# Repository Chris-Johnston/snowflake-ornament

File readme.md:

# Snowflake-Ornament

A snowflake shaped Xmas ornament with blinking LEDs.

This uses an ATTiny85 to drive 6 blue LEDs which are multiplexed.
There's a button on the front which is used to toggle display modes
and sleep.

When sleeping, the ornament uses about 200 microamps of current, little enough to run
off of a coin cell battery for about 1000 hours (in reality, probably less. I don't know, I didn't measure it)! While running, it uses about 2 milliamps,
which could last for about 120 hours.

The part was designed using KiCad. The shape of the PCB was generated with
[svg2mod]. The [outline of the board was modified from Wikipedia (Public Domain)](https://en.wikipedia.org/wiki/File:Snow_flake.svg), I added a hexagon in the
center to make room for the button, ATTiny85, and battery.

[svg2mod]: https://github.com/svg2mod/svg2mod

## Requirements

I use [damellis/attiny] for ATTiny85 support in the Arduino editor (via the VSCode extension).

[damellis/attiny]: https://github.com/damellis/attiny

## Bill of Materials

| Reference | Item |
| --------- | ---- |
| U1 | Attiny85V |
| R1, R2, R3, R4 | 50 ohm 1206 resistor |
| R5 | 10k 1206 resistor |
| C1 | 1 uf 1206 capacitor |
| D1 - D6 | 0603 LED |
| SW1 | 6x6mm SMD Pushbutton |
| BT1 | CR2023 Battery Holder |

Yes, the traces aren't parallel to the edges of the board, and yes it bugs me too.

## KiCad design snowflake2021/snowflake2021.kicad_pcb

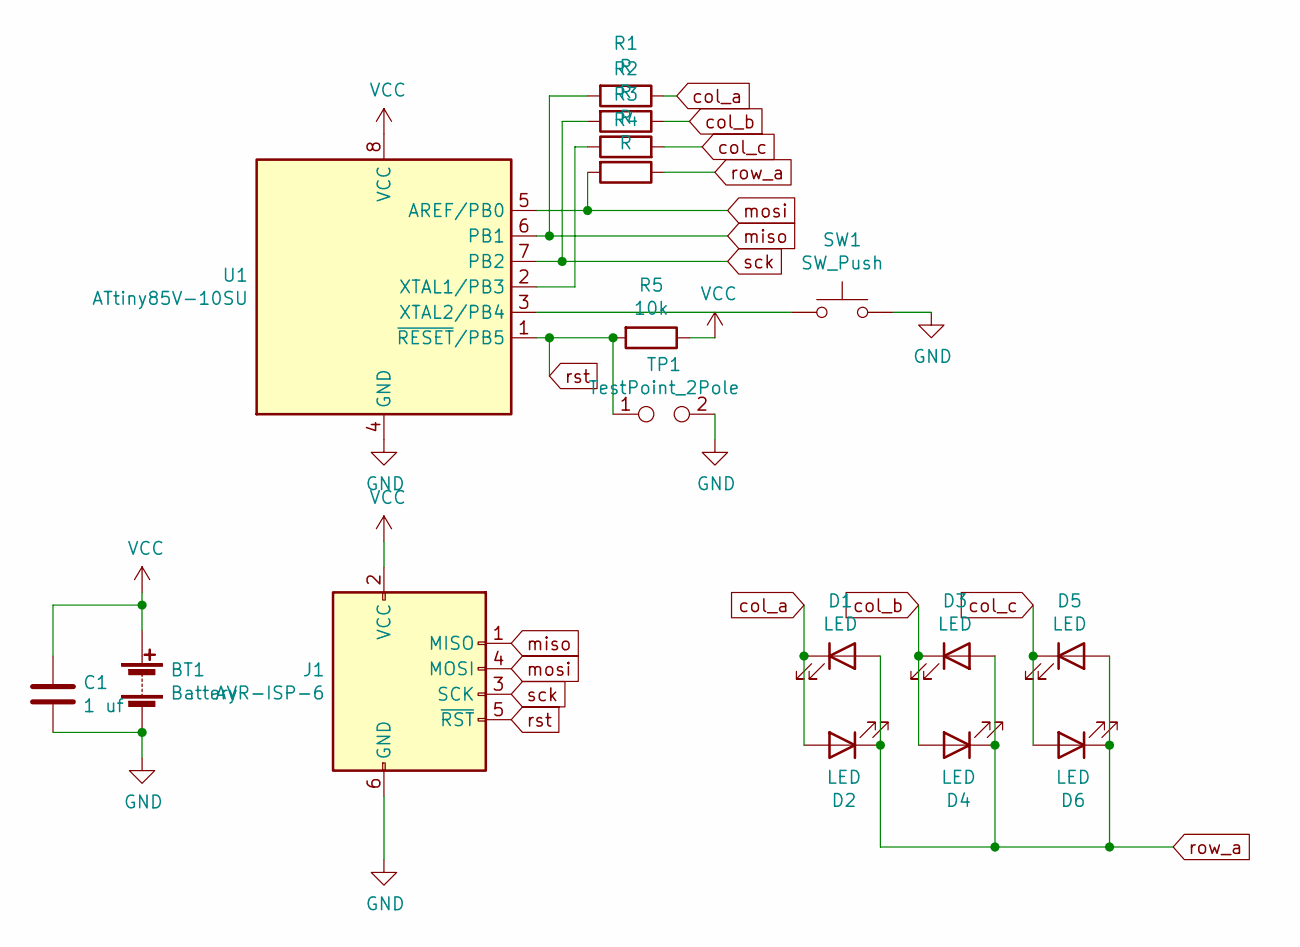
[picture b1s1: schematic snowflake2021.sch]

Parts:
BT1: Battery; BatteryHolder_ComfortableElectronic_CH273-2450_1x2450
C1: 1 uf; C_1206_3216Metric_Pad1.42x1.75mm_HandSolder
D1, D2, D3, D4, D5, D6: LED; LED_0603_1608Metric_Pad1.05x0.95mm_HandSolder
J1: AVR-ISP-6; PinHeader_2x03_P2.54mm_Vertical
R1, R2, R3, R4: R; R_1206_3216Metric_Pad1.42x1.75mm_HandSolder
R5: 10k; R_1206_3216Metric_Pad1.42x1.75mm_HandSolder
SW1: SW_Push; SW_Push_1P1T_NO_6x6mm_H9.5mm
TP1: TestPoint_2Pole; SolderJumper-2_P1.3mm_Open_Pad1.0x1.5mm
U1: ATtiny85V-10SU; SOIJ-8_5.3x5.3mm_P1.27mm

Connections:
GND: BT1.2 (-), C1.2, J1.6 (GND), SW1.2, TP1.2, U1.4 (GND); also elsewhere on the board
unnamed: R3.1, U1.2 (XTAL1/PB3)
unnamed: SW1.1, U1.3 (XTAL2/PB4)
VCC: BT1.1 (+), C1.1, J1.2 (VCC), R5.1, U1.8 (VCC)
col_a: D1.1 (K), D2.2 (A), R1.1
col_b: D3.1 (K), D4.2 (A), R2.1
col_c: D5.1 (K), D6.2 (A), R3.2
miso: J1.1 (MISO), R1.2, U1.6 (PB1)
mosi: J1.4 (MOSI), R4.2, U1.5 (AREF/PB0)
row_a: D1.2 (A), D2.1 (K), D3.2 (A), D4.1 (K), D5.2 (A), D6.1 (K), R4.1
rst: J1.5 (~RST), R5.2, TP1.1, U1.1 (~RESET~/PB5); also elsewhere on the board
sck: J1.3 (SCK), R2.2, U1.7 (PB2)

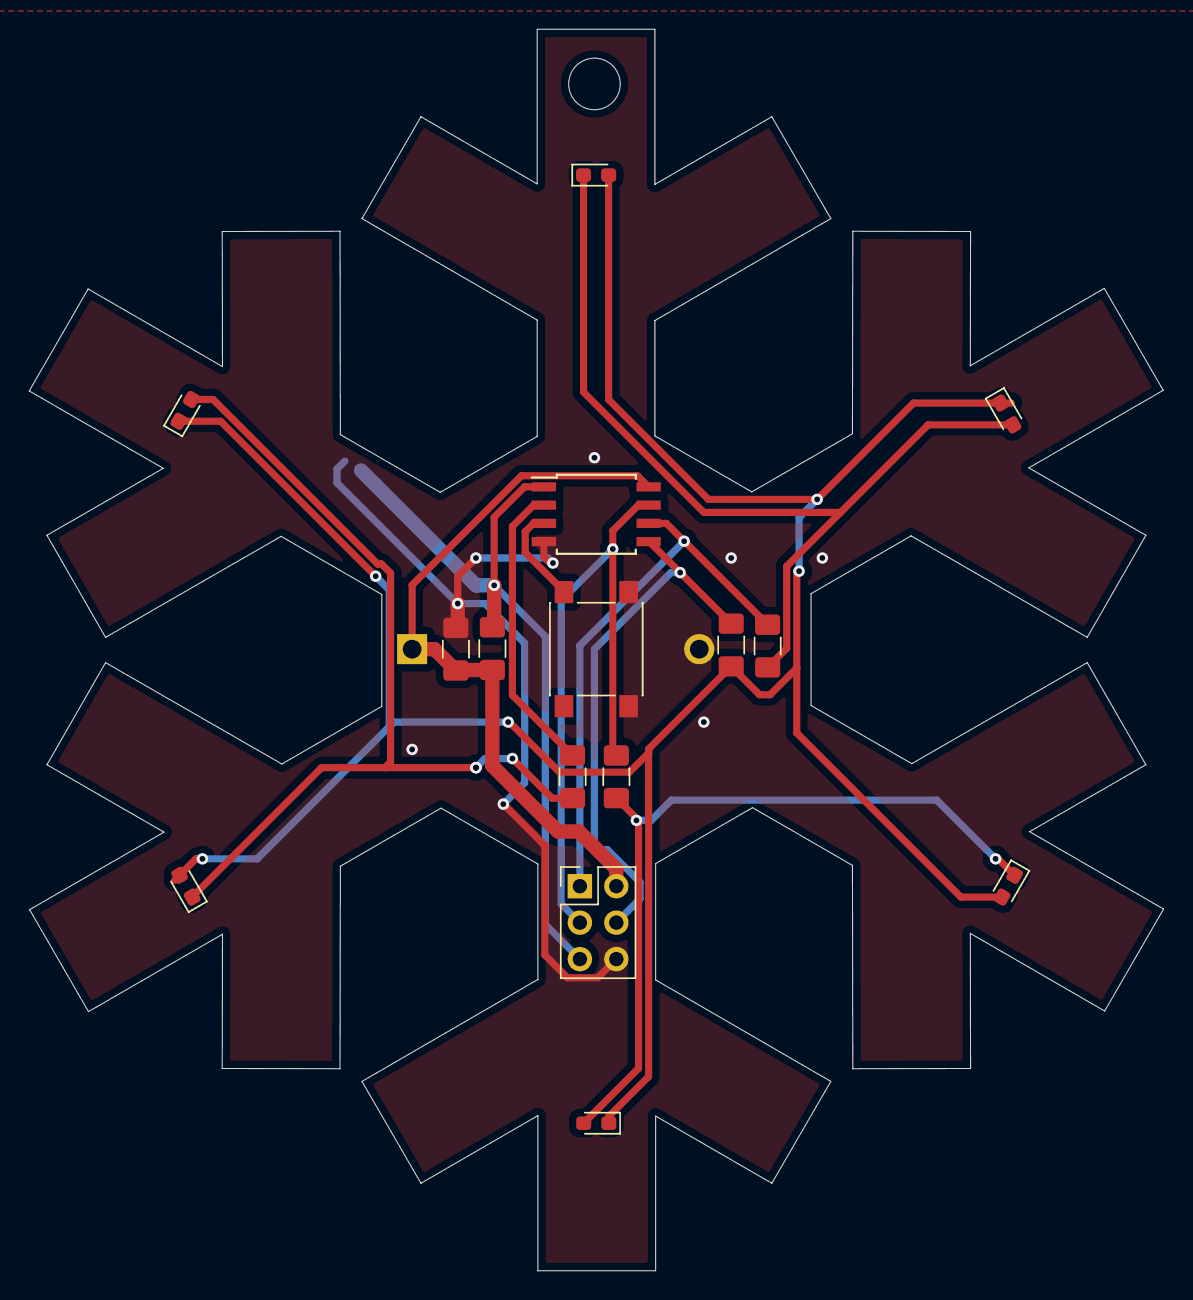
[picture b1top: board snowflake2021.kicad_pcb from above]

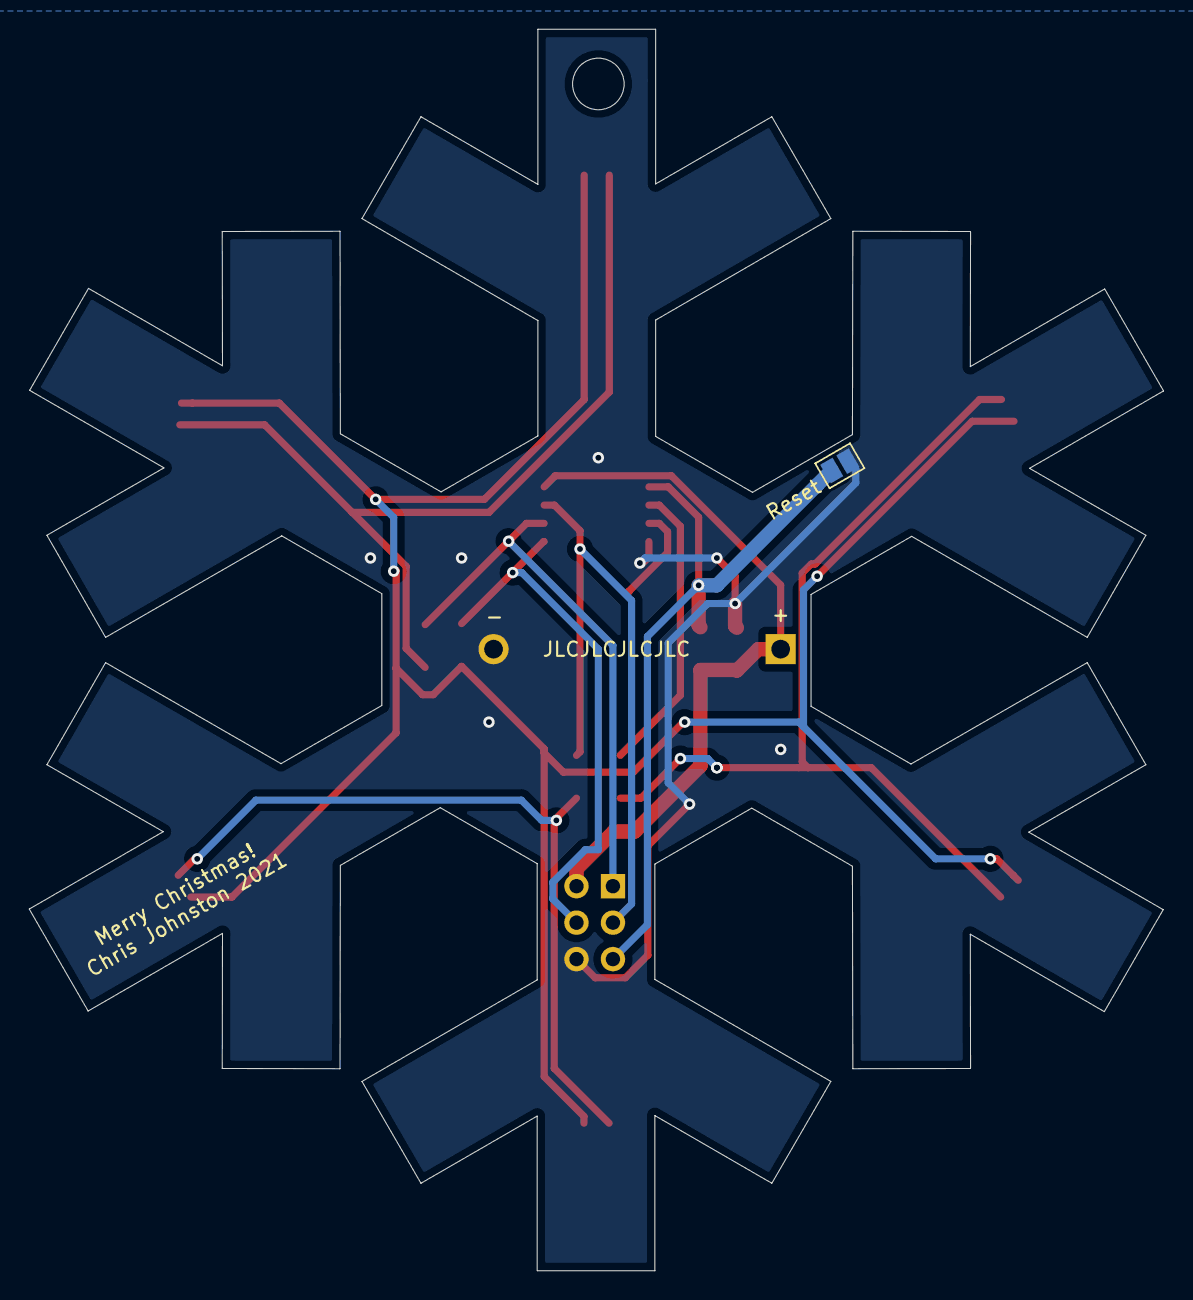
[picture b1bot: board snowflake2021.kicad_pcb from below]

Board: 2 copper layers, 79.0 x 86.5 mm, 18 parts (2 on the bottom side), 12 nets.

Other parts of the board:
Reset: TestPoint_2Pole; SolderJumper-2_P1.3mm_Open_Pad1.0x1.5mm
svg2mod: G***; snowflake

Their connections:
GND: Reset.2; also elsewhere on the board
rst: Reset.1; also elsewhere on the board

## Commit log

2021-11-14 ship it
2021-12-11 it lives!!!
2021-12-11 add patterns
2021-12-12 add todo
2021-12-12 add readme and images
2021-12-12 add .gitignore
2021-12-12 apply gitignore
2021-12-12 remove old gerber
2021-12-12 add thumbnail image
2021-12-12 remove cache file
2021-12-12 add more patterns
2021-12-12 add more documentation
2021-12-12 Create LICENSE
2021-12-12 fix typo in the path to the schematic screenshot
2021-12-26 Add image of snowflake ornament when it was snowing outside
